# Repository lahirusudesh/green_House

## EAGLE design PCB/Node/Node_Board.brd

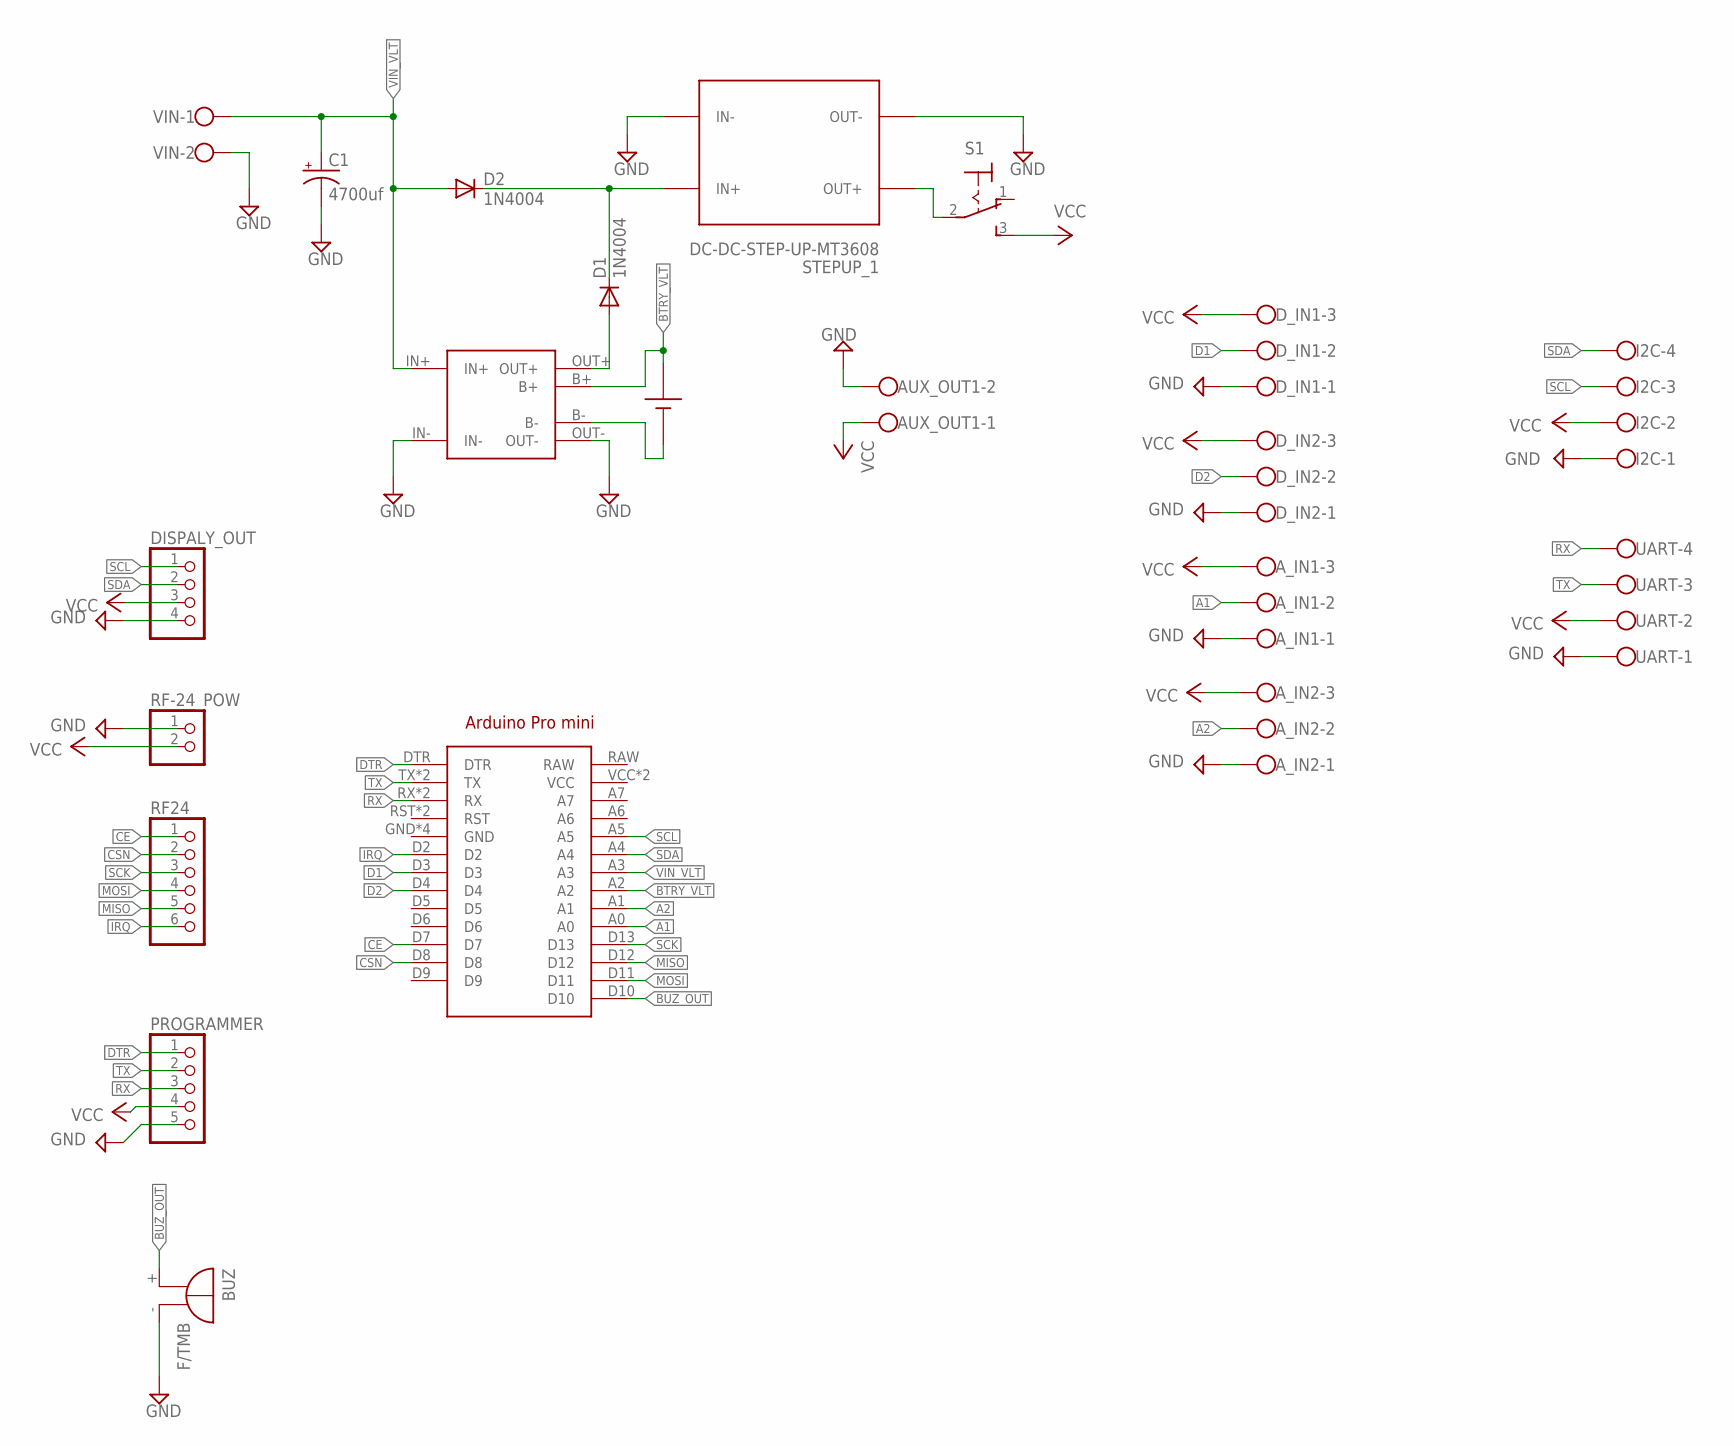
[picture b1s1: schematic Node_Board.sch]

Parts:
ARDUINO1: ARDUINO_PRO_MINI
AUX_OUT1: W237-102
A_IN1, A_IN2: W237-103
BATTRY: 18650CABLE; 18650-CASE-CABLE
BUZ: F/TMB
C1: 4700uf; E3,5-8
D1, D2: 1N4004; DO41-10
DISPALY_OUT: PINHD-1X4; 1X04
D_IN1, D_IN2: W237-103
I2C: W237-4
PROGRAMMER: PINHD-1X5; 1X05
RF24: PINHD-1X6; 1X06
RF-24_POW: PINHD-1X2; 1X02
S1: M9040P
STEPUP_1: DC-DC-STEP-UP-MT3608
U$2: TP4056-MODULE; TP4056-LITHIUM-PROTECTED-MODULE
UART: W237-4
VIN: W237-102

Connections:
A1: ARDUINO1.A0, A_IN1.2
A2: ARDUINO1.A1, A_IN2.2
BTRY_VLT: ARDUINO1.A2, BATTRY.POS, U$2.B+
BUZ_OUT: ARDUINO1.D10, BUZ.+
CE: ARDUINO1.D7, RF24.1
CSN: ARDUINO1.D8, RF24.2
D1: ARDUINO1.D3, D_IN1.2
D2: ARDUINO1.D4, D_IN2.2
DTR: ARDUINO1.DTR, PROGRAMMER.1
GND: ARDUINO1.GND, ARDUINO1.GND@1 (GND), ARDUINO1.GND@2 (GND), ARDUINO1.GND@3 (GND), AUX_OUT1.2, A_IN1.1, A_IN2.1, BUZ.-, C1.-, DISPALY_OUT.4, D_IN1.1, D_IN2.1, I2C.1, PROGRAMMER.5, RF-24_POW.1, STEPUP_1.IN-, STEPUP_1.OUT-, U$2.IN-, U$2.OUT-, UART.1, VIN.2
IRQ: ARDUINO1.D2, RF24.6
MISO: ARDUINO1.D12, RF24.5
MOSI: ARDUINO1.D11, RF24.4
unnamed: D1.C, D2.C, STEPUP_1.IN+
unnamed: BATTRY.NEG, U$2.B-
unnamed: D1.A, U$2.OUT+
unnamed: S1.2, STEPUP_1.OUT+
RX: ARDUINO1.RX, ARDUINO1.RX@1 (RX), PROGRAMMER.3, UART.4
SCK: ARDUINO1.D13, RF24.3
SCL: ARDUINO1.A5, DISPALY_OUT.1, I2C.3
SDA: ARDUINO1.A4, DISPALY_OUT.2, I2C.4
TX: ARDUINO1.TX, ARDUINO1.TX@1 (TX), PROGRAMMER.2, UART.3
VCC: ARDUINO1.VCC, ARDUINO1.VCC@1 (VCC), AUX_OUT1.1, A_IN1.3, A_IN2.3, DISPALY_OUT.3, D_IN1.3, D_IN2.3, I2C.2, PROGRAMMER.4, RF-24_POW.2, S1.3 (S), UART.2
VIN_VLT: ARDUINO1.A3, C1.+, D2.A, U$2.IN+, VIN.1

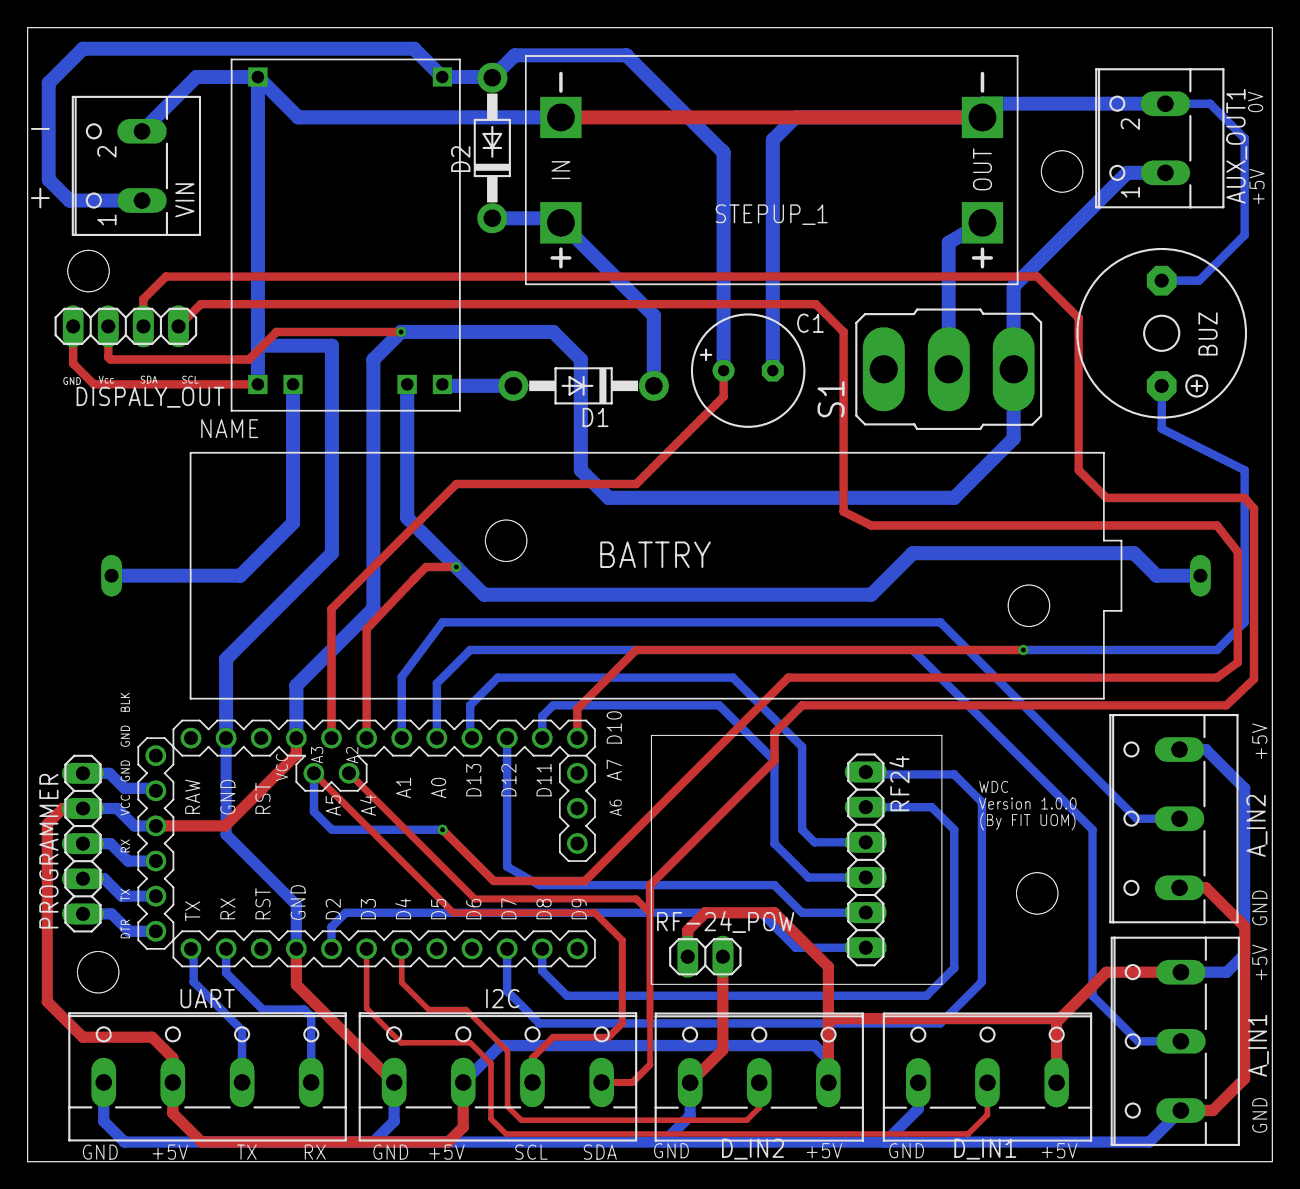
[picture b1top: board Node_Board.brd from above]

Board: 2 copper layers, 90.0 x 82.0 mm, 21 parts (0 on the bottom side), 24 nets.

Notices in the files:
parts and their libraries:
diy-modules: Released under the Creative Commons Attribution 4.0 International License: http://creativecommons.org/licenses/by/4.0
